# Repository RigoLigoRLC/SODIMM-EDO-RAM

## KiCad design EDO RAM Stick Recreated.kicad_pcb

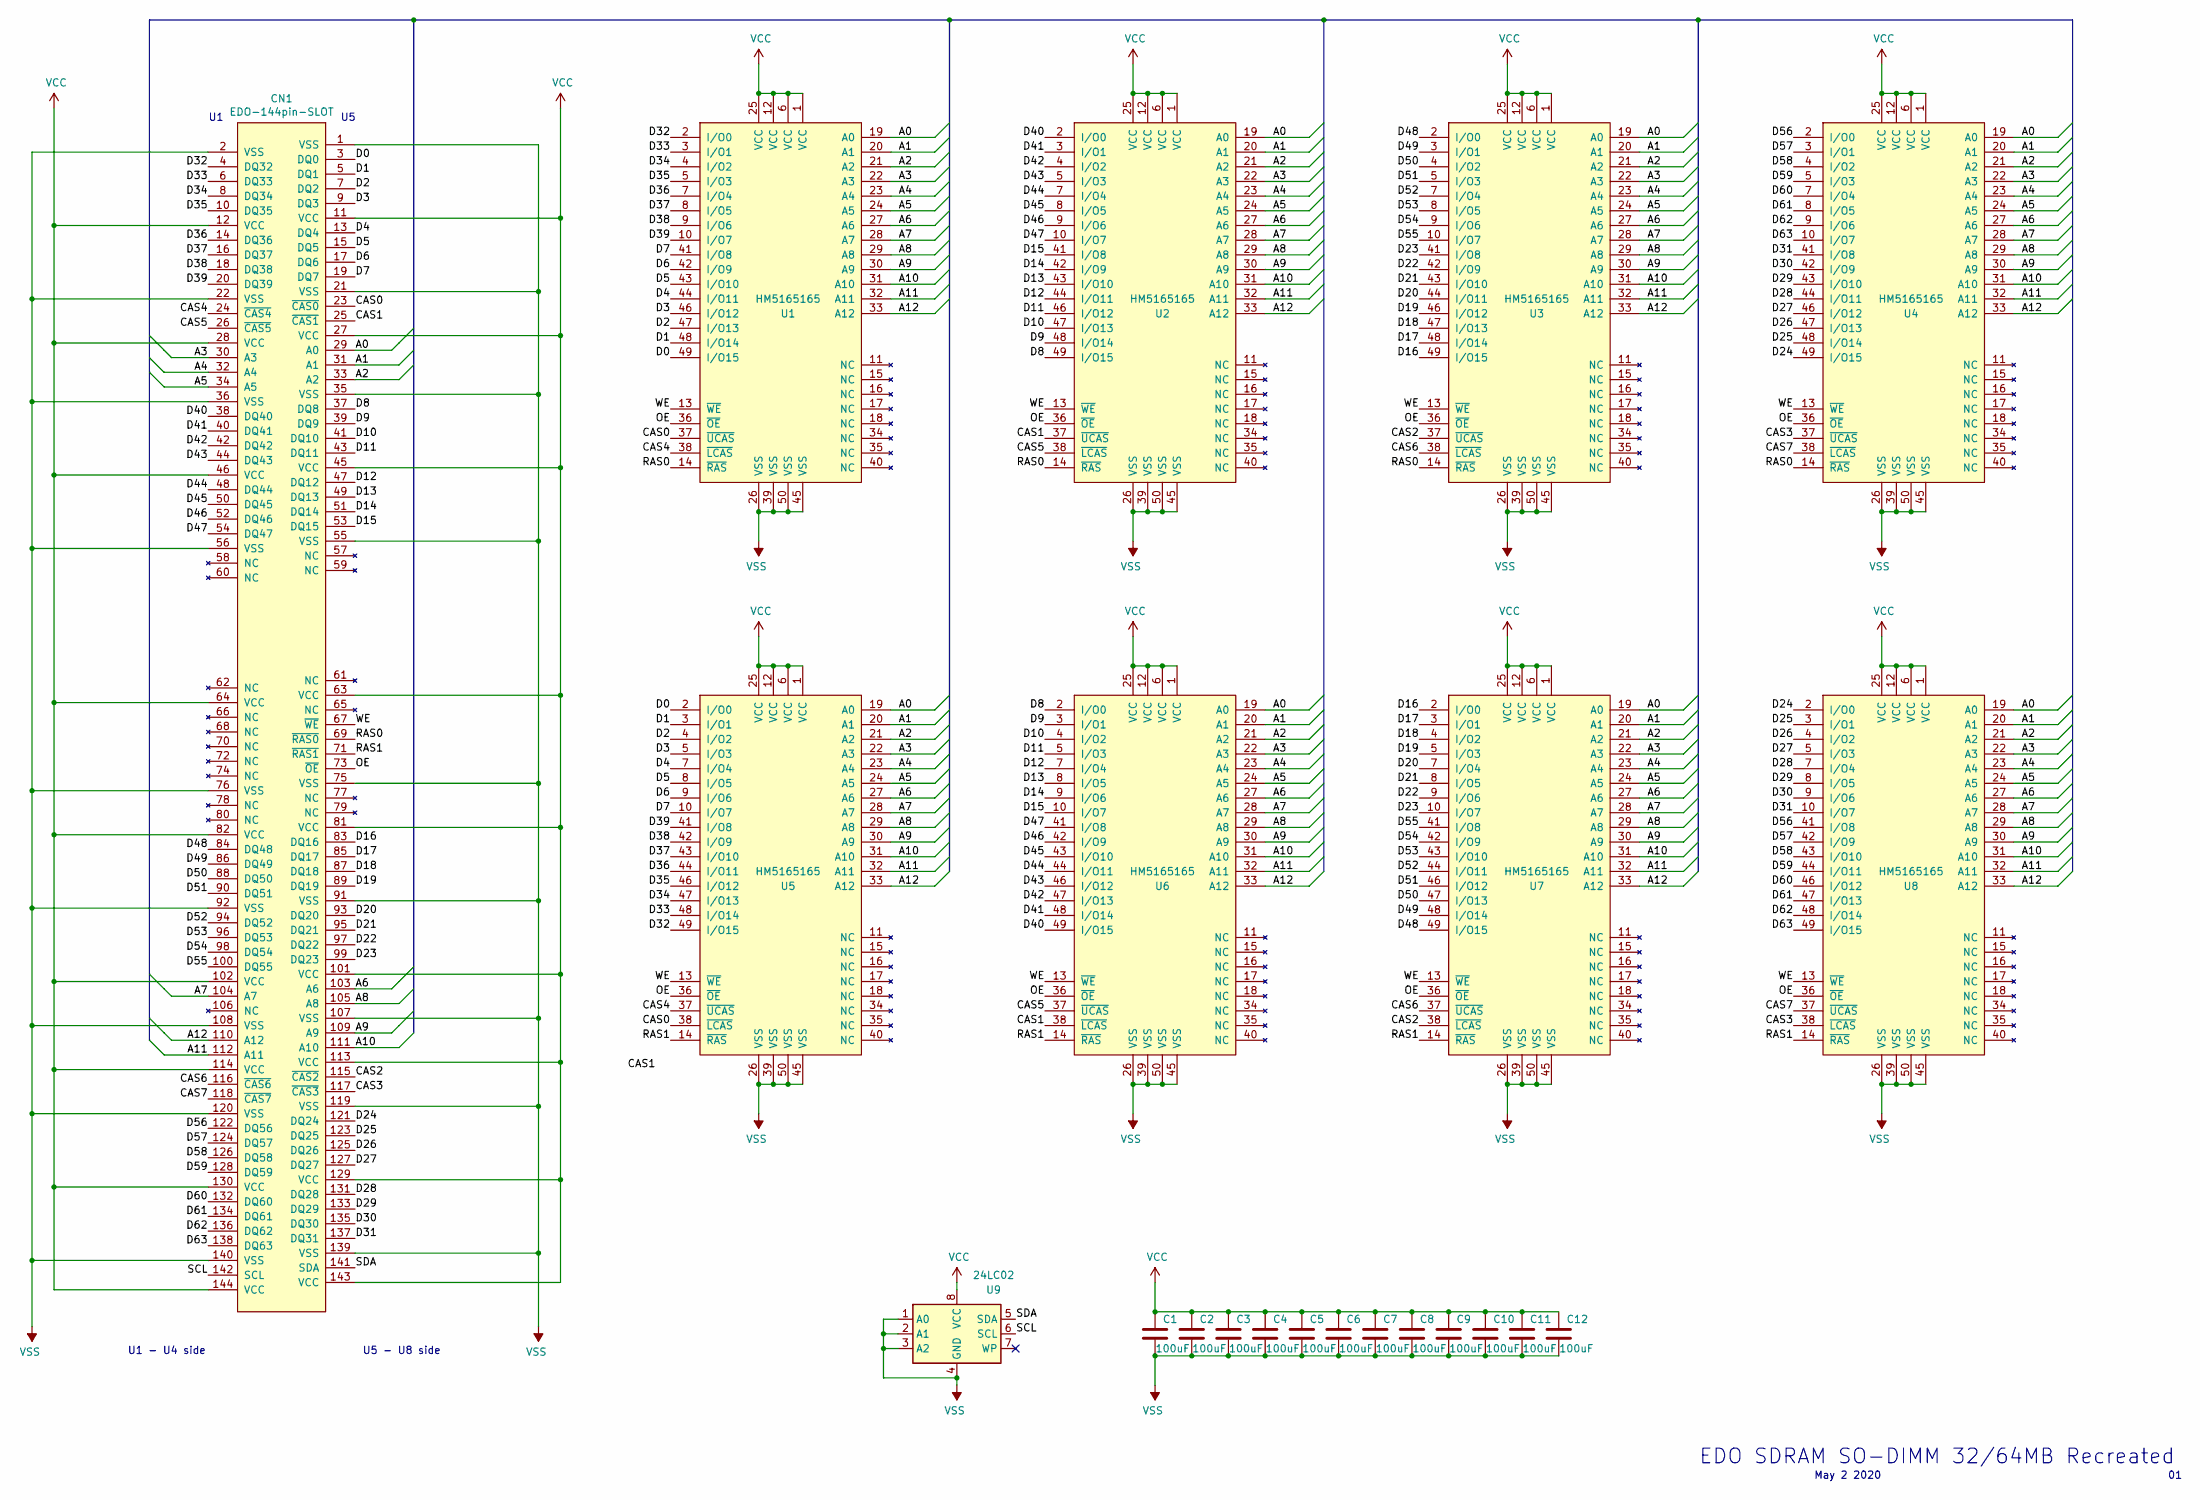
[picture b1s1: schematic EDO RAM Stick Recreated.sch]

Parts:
C1, C2, C3, C4, C5, C6, C7, C8, C9, C10, C11, C12: 100uF; C_0603_1608Metric_Pad1.05x0.95mm_HandSolder
CN1: EDO-144pin-SLOT; EDO_SODIMM_144pin
U1, U2, U3, U4, U5, U6, U7, U8: HM5165165; SOIC-50
U9: 24LC02; SOIC-8_3.9x4.9mm_P1.27mm

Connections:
/A0: CN1.29 (A0), U1.19 (A0), U2.19 (A0), U3.19 (A0), U4.19 (A0), U5.19 (A0), U6.19 (A0), U7.19 (A0), U8.19 (A0)
/A1: CN1.31 (A1), U1.20 (A1), U2.20 (A1), U3.20 (A1), U4.20 (A1), U5.20 (A1), U6.20 (A1), U7.20 (A1), U8.20 (A1)
/A2: CN1.33 (A2), U1.21 (A2), U2.21 (A2), U3.21 (A2), U4.21 (A2), U5.21 (A2), U6.21 (A2), U7.21 (A2), U8.21 (A2)
/A3: CN1.30 (A3), U1.22 (A3), U2.22 (A3), U3.22 (A3), U4.22 (A3), U5.22 (A3), U6.22 (A3), U7.22 (A3), U8.22 (A3)
/A4: CN1.32 (A4), U1.23 (A4), U2.23 (A4), U3.23 (A4), U4.23 (A4), U5.23 (A4), U6.23 (A4), U7.23 (A4), U8.23 (A4)
/A5: CN1.34 (A5), U1.24 (A5), U2.24 (A5), U3.24 (A5), U4.24 (A5), U5.24 (A5), U6.24 (A5), U7.24 (A5), U8.24 (A5)
/A6: CN1.103 (A6), U1.27 (A6), U2.27 (A6), U3.27 (A6), U4.27 (A6), U5.27 (A6), U6.27 (A6), U7.27 (A6), U8.27 (A6)
/A7: CN1.104 (A7), U1.28 (A7), U2.28 (A7), U3.28 (A7), U4.28 (A7), U5.28 (A7), U6.28 (A7), U7.28 (A7), U8.28 (A7)
/A8: CN1.105 (A8), U1.29 (A8), U2.29 (A8), U3.29 (A8), U4.29 (A8), U5.29 (A8), U6.29 (A8), U7.29 (A8), U8.29 (A8)
/A9: CN1.109 (A9), U1.30 (A9), U2.30 (A9), U3.30 (A9), U4.30 (A9), U5.30 (A9), U6.30 (A9), U7.30 (A9), U8.30 (A9)
/A10: CN1.111 (A10), U1.31 (A10), U2.31 (A10), U3.31 (A10), U4.31 (A10), U5.31 (A10), U6.31 (A10), U7.31 (A10), U8.31 (A10)
/A11: CN1.112 (A11), U1.32 (A11), U2.32 (A11), U3.32 (A11), U4.32 (A11), U5.32 (A11), U6.32 (A11), U7.32 (A11), U8.32 (A11)
/A12: CN1.110 (A12), U1.33 (A12), U2.33 (A12), U3.33 (A12), U4.33 (A12), U5.33 (A12), U6.33 (A12), U7.33 (A12), U8.33 (A12)
/CAS0: CN1.23 (~CAS0), U1.37 (~UCAS), U5.38 (~LCAS)
/CAS1: CN1.25 (~CAS1), U2.37 (~UCAS), U6.38 (~LCAS)
/CAS2: CN1.115 (~CAS2), U3.37 (~UCAS), U7.38 (~LCAS)
/CAS3: CN1.117 (~CAS3), U4.37 (~UCAS), U8.38 (~LCAS)
/CAS4: CN1.24 (~CAS4), U1.38 (~LCAS), U5.37 (~UCAS)
/CAS5: CN1.26 (~CAS5), U2.38 (~LCAS), U6.37 (~UCAS)
/CAS6: CN1.116 (~CAS6), U3.38 (~LCAS), U7.37 (~UCAS)
/CAS7: CN1.118 (~CAS7), U4.38 (~LCAS), U8.37 (~UCAS)
/D0: CN1.3 (DQ0), U1.49 (I/O15), U5.2 (I/O0)
/D1: CN1.5 (DQ1), U1.48 (I/O14), U5.3 (I/O1)
/D2: CN1.7 (DQ2), U1.47 (I/O13), U5.4 (I/O2)
/D3: CN1.9 (DQ3), U1.46 (I/O12), U5.5 (I/O3)
/D4: CN1.13 (DQ4), U1.44 (I/O11), U5.7 (I/O4)
/D5: CN1.15 (DQ5), U1.43 (I/O10), U5.8 (I/O5)
/D6: CN1.17 (DQ6), U1.42 (I/O9), U5.9 (I/O6)
/D7: CN1.19 (DQ7), U1.41 (I/O8), U5.10 (I/O7)
/D8: CN1.37 (DQ8), U2.49 (I/O15), U6.2 (I/O0)
/D9: CN1.39 (DQ9), U2.48 (I/O14), U6.3 (I/O1)
/D10: CN1.41 (DQ10), U2.47 (I/O13), U6.4 (I/O2)
/D11: CN1.43 (DQ11), U2.46 (I/O12), U6.5 (I/O3)
/D12: CN1.47 (DQ12), U2.44 (I/O11), U6.7 (I/O4)
/D13: CN1.49 (DQ13), U2.43 (I/O10), U6.8 (I/O5)
/D14: CN1.51 (DQ14), U2.42 (I/O9), U6.9 (I/O6)
/D15: CN1.53 (DQ15), U2.41 (I/O8), U6.10 (I/O7)
/D16: CN1.83 (DQ16), U3.49 (I/O15), U7.2 (I/O0)
/D17: CN1.85 (DQ17), U3.48 (I/O14), U7.3 (I/O1)
/D18: CN1.87 (DQ18), U3.47 (I/O13), U7.4 (I/O2)
/D19: CN1.89 (DQ19), U3.46 (I/O12), U7.5 (I/O3)
/D20: CN1.93 (DQ20), U3.44 (I/O11), U7.7 (I/O4)
/D21: CN1.95 (DQ21), U3.43 (I/O10), U7.8 (I/O5)
/D22: CN1.97 (DQ22), U3.42 (I/O9), U7.9 (I/O6)
/D23: CN1.99 (DQ23), U3.41 (I/O8), U7.10 (I/O7)
/D24: CN1.121 (DQ24), U4.49 (I/O15), U8.2 (I/O0)
/D25: CN1.123 (DQ25), U4.48 (I/O14), U8.3 (I/O1)
/D26: CN1.125 (DQ26), U4.47 (I/O13), U8.4 (I/O2)
/D27: CN1.127 (DQ27), U4.46 (I/O12), U8.5 (I/O3)
/D28: CN1.131 (DQ28), U4.44 (I/O11), U8.7 (I/O4)
/D29: CN1.133 (DQ29), U4.43 (I/O10), U8.8 (I/O5)
/D30: CN1.135 (DQ30), U4.42 (I/O9), U8.9 (I/O6)
/D31: CN1.137 (DQ31), U4.41 (I/O8), U8.10 (I/O7)
/D32: CN1.4 (DQ32), U1.2 (I/O0), U5.49 (I/O15)
/D33: CN1.6 (DQ33), U1.3 (I/O1), U5.48 (I/O14)
/D34: CN1.8 (DQ34), U1.4 (I/O2), U5.47 (I/O13)
/D35: CN1.10 (DQ35), U1.5 (I/O3), U5.46 (I/O12)
/D36: CN1.14 (DQ36), U1.7 (I/O4), U5.44 (I/O11)
/D37: CN1.16 (DQ37), U1.8 (I/O5), U5.43 (I/O10)
/D38: CN1.18 (DQ38), U1.9 (I/O6), U5.42 (I/O9)
/D39: CN1.20 (DQ39), U1.10 (I/O7), U5.41 (I/O8)
/D40: CN1.38 (DQ40), U2.2 (I/O0), U6.49 (I/O15)
/D41: CN1.40 (DQ41), U2.3 (I/O1), U6.48 (I/O14)
/D42: CN1.42 (DQ42), U2.4 (I/O2), U6.47 (I/O13)
/D43: CN1.44 (DQ43), U2.5 (I/O3), U6.46 (I/O12)
/D44: CN1.48 (DQ44), U2.7 (I/O4), U6.44 (I/O11)
/D45: CN1.50 (DQ45), U2.8 (I/O5), U6.43 (I/O10)
/D46: CN1.52 (DQ46), U2.9 (I/O6), U6.42 (I/O9)
/D47: CN1.54 (DQ47), U2.10 (I/O7), U6.41 (I/O8)
/D48: CN1.84 (DQ48), U3.2 (I/O0), U7.49 (I/O15)
/D49: CN1.86 (DQ49), U3.3 (I/O1), U7.48 (I/O14)
/D50: CN1.88 (DQ50), U3.4 (I/O2), U7.47 (I/O13)
/D51: CN1.90 (DQ51), U3.5 (I/O3), U7.46 (I/O12)
/D52: CN1.94 (DQ52), U3.7 (I/O4), U7.44 (I/O11)
/D53: CN1.96 (DQ53), U3.8 (I/O5), U7.43 (I/O10)
/D54: CN1.98 (DQ54), U3.9 (I/O6), U7.42 (I/O9)
/D55: CN1.100 (DQ55), U3.10 (I/O7), U7.41 (I/O8)
/D56: CN1.122 (DQ56), U4.2 (I/O0), U8.41 (I/O8)
/D57: CN1.124 (DQ57), U4.3 (I/O1), U8.42 (I/O9)
/D58: CN1.126 (DQ58), U4.4 (I/O2), U8.43 (I/O10)
/D59: CN1.128 (DQ59), U4.5 (I/O3), U8.44 (I/O11)
/D60: CN1.132 (DQ60), U4.7 (I/O4), U8.46 (I/O12)
/D61: CN1.134 (DQ61), U4.8 (I/O5), U8.47 (I/O13)
/D62: CN1.136 (DQ62), U4.9 (I/O6), U8.48 (I/O14)
/D63: CN1.138 (DQ63), U4.10 (I/O7), U8.49 (I/O15)
/OE: CN1.73 (~OE), U1.36 (~OE), U2.36 (~OE), U3.36 (~OE), U4.36 (~OE), U5.36 (~OE), U6.36 (~OE), U7.36 (~OE), U8.36 (~OE)
/RAS0: CN1.69 (~RAS0), U1.14 (~RAS), U2.14 (~RAS), U3.14 (~RAS), U4.14 (~RAS)
/RAS1: CN1.71 (~RAS1), U5.14 (~RAS), U6.14 (~RAS), U7.14 (~RAS), U8.14 (~RAS)
/SCL: CN1.142 (SCL), U9.6 (SCL)
/SDA: CN1.141 (SDA), U9.5 (SDA)
/WE: CN1.67 (~WE), U1.13 (~WE), U2.13 (~WE), U3.13 (~WE), U4.13 (~WE), U5.13 (~WE), U6.13 (~WE), U7.13 (~WE), U8.13 (~WE)
VCC: C1.1, C2.1, C3.1, C4.1, C5.1, C6.1, C7.1, C8.1, C9.1, C10.1, C11.1, C12.1, CN1.11 (VCC), CN1.12 (VCC), CN1.27 (VCC), CN1.28 (VCC), CN1.45 (VCC), CN1.46 (VCC), CN1.63 (VCC), CN1.64 (VCC), CN1.81 (VCC), CN1.82 (VCC), CN1.101 (VCC), CN1.102 (VCC), CN1.113 (VCC), CN1.114 (VCC), CN1.129 (VCC), CN1.130 (VCC), CN1.143 (VCC), CN1.144 (VCC), U1.1 (VCC), U1.6 (VCC), U1.12 (VCC), U1.25 (VCC), U2.1 (VCC), U2.6 (VCC), U2.12 (VCC), U2.25 (VCC), U3.1 (VCC), U3.6 (VCC), U3.12 (VCC), U3.25 (VCC), U4.1 (VCC), U4.6 (VCC), U4.12 (VCC), U4.25 (VCC), U5.1 (VCC), U5.6 (VCC), U5.12 (VCC), U5.25 (VCC), U6.1 (VCC), U6.6 (VCC), U6.12 (VCC), U6.25 (VCC), U7.1 (VCC), U7.6 (VCC), U7.12 (VCC), U7.25 (VCC), U8.1 (VCC), U8.6 (VCC), U8.12 (VCC), U8.25 (VCC), U9.8 (VCC)
VSS: C1.2, C2.2, C3.2, C4.2, C5.2, C6.2, C7.2, C8.2, C9.2, C10.2, C11.2, C12.2, CN1.1 (VSS), CN1.2 (VSS), CN1.21 (VSS), CN1.22 (VSS), CN1.35 (VSS), CN1.36 (VSS), CN1.55 (VSS), CN1.56 (VSS), CN1.75 (VSS), CN1.76 (VSS), CN1.91 (VSS), CN1.92 (VSS), CN1.107 (VSS), CN1.108 (VSS), CN1.119 (VSS), CN1.120 (VSS), CN1.139 (VSS), CN1.140 (VSS), U1.26 (VSS), U1.39 (VSS), U1.45 (VSS), U1.50 (VSS), U2.26 (VSS), U2.39 (VSS), U2.45 (VSS), U2.50 (VSS), U3.26 (VSS), U3.39 (VSS), U3.45 (VSS), U3.50 (VSS), U4.26 (VSS), U4.39 (VSS), U4.45 (VSS), U4.50 (VSS), U5.26 (VSS), U5.39 (VSS), U5.45 (VSS), U5.50 (VSS), U6.26 (VSS), U6.39 (VSS), U6.45 (VSS), U6.50 (VSS), U7.26 (VSS), U7.39 (VSS), U7.45 (VSS), U7.50 (VSS), U8.26 (VSS), U8.39 (VSS), U8.45 (VSS), U8.50 (VSS), U9.1 (A0), U9.2 (A1), U9.3 (A2), U9.4 (GND)

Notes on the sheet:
U1 - U4 side
U5 - U8 side
EDO SDRAM SO-DIMM 32/64MB Recreated
May 2 2020

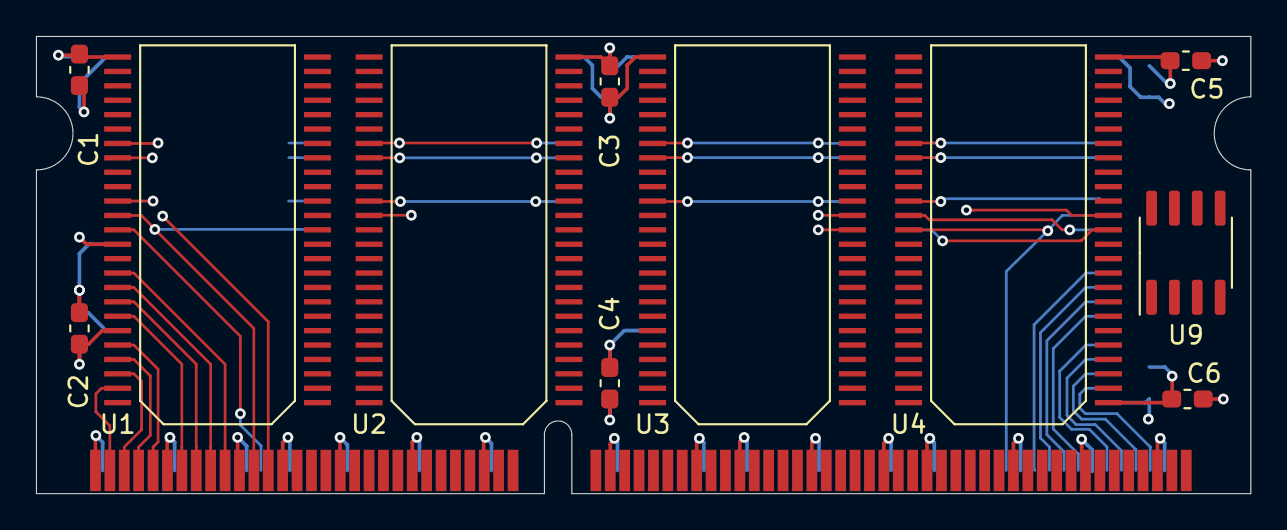
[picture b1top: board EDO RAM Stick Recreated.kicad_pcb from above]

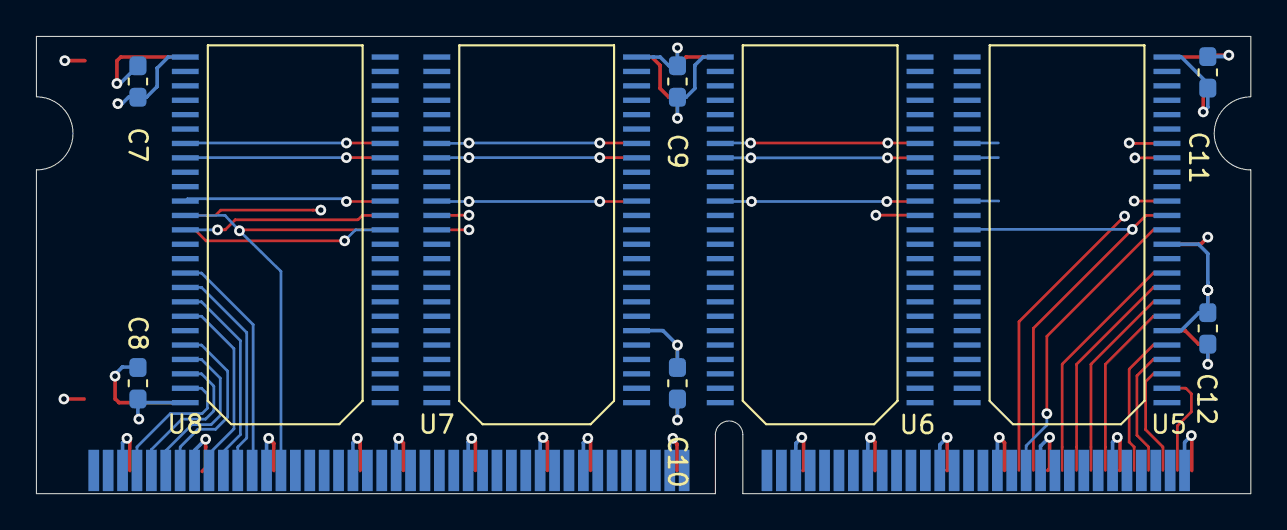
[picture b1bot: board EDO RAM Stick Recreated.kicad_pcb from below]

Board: 4 copper layers, 67.5 x 25.4 mm, 22 parts (10 on the bottom side), 93 nets.

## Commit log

2019-09-13 The initial commit.
2019-09-13 U1 Connections
2019-09-13 Back Side Left IC Wiring (WIP).
2019-09-13 Fixed IC Positions.
2019-09-15 Surface layer Third IC F/B Complete
2019-09-15 Added caps and SPD ROM.
2020-12-31 First connected version
2020-12-31 edit1
2020-12-31 ...Some random commit
2020-12-31 mockup of spd
